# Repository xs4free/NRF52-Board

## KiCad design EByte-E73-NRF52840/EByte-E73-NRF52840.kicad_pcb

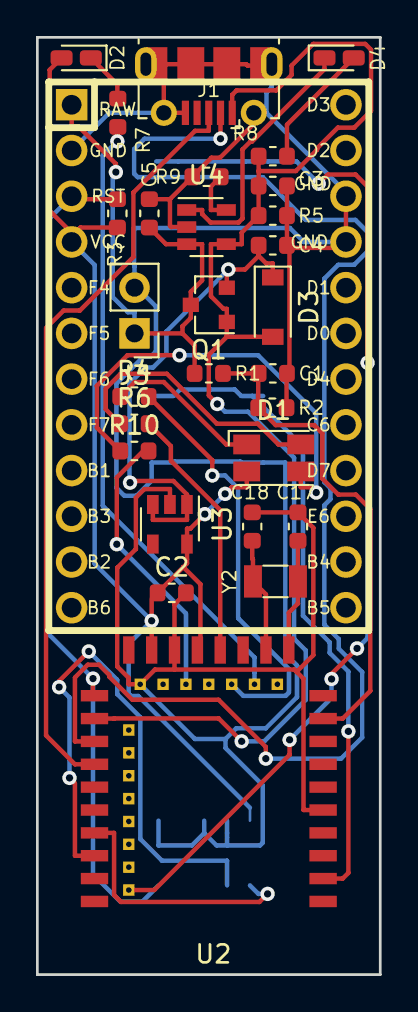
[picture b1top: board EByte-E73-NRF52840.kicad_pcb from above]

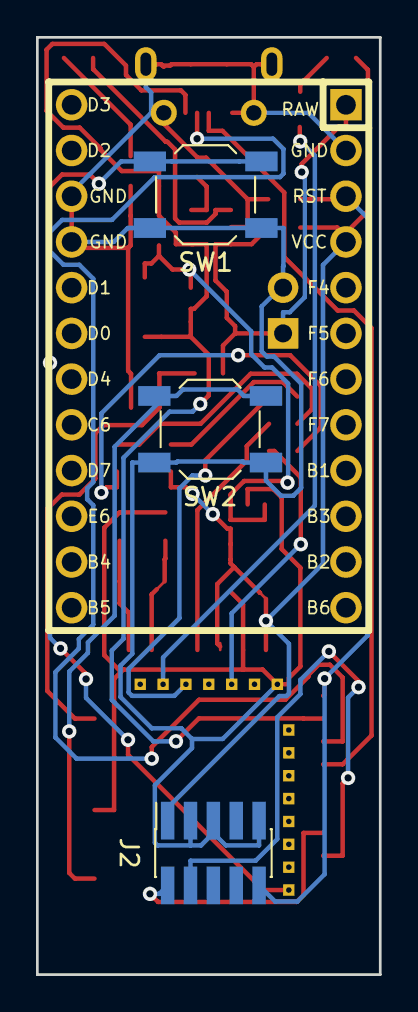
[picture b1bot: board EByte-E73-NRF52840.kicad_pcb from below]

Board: 2 copper layers, 19.1 x 52.1 mm, 32 parts (3 on the bottom side), 26 nets.

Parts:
C1: 1nF; C_0603_1608Metric
C2, C3, C4, C5: 10uF; C_0603_1608Metric
C17, C18: 12pF; C_0603_1608Metric
D1: HQ17-2303BGRC; LED_Avago_PLCC4_3.2x2.8mm_CW
D2, D4: LED; LED_0603_1608Metric_Castellated
D3: D_Schottky; D_SOD-123
J1: USB_B_Micro; USB_Micro-B_Molex-105017-0001
J2: SWD Header; PinSocket_2x05_P1.27mm_Vertical_SMD
J3: Conn_01x02; PinHeader_1x02_P2.54mm_Vertical
Q1: TP0610T; SOT-23
R1: 806k; R_0603_1608Metric
R2: 2M; R_0603_1608Metric
R3, R9: 10k; R_0603_1608Metric
R4: 1k2; R_0603_1608Metric
R5: 100k; R_0603_1608Metric
R6: 2k2; R_0603_1608Metric
R7, R8: 330; R_0603_1608Metric
R10: 330R; R_0603_1608Metric
SW1: DFU; SW_TACT_ALPS_SKQGABE010
SW2: FRST; SW_TACT_ALPS_SKQGABE010
U1: ProMicro; Pro_Micro
U2: E73-2G4M08S1C; 2G4M08S1C
U3: AP2112K-3.3; SOT-23-5
U4: TP4054ST; SOT-23-5
Y2: 32.768kHz; Crystal_SMD_3215-2Pin_3.2x1.5mm

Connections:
/D+: J1.3, U2.31
/D-: J1.2, U2.29
/LED1: R7.2, U2.14
/LED2B: R10.2, U2.20
/LED2G: R6.2, U2.17
/LED2R: R4.2, U2.16
/P0.31: C1.1, R1.2, R2.1, U2.9
/P1.10: SW2.2, U2.2
/RESET: J2.10, R3.2, U1.3, U2.26
/SW1: SW1.2, U2.42
/SWDCLK: J2.4, U2.39
/SWDIO: J2.2, U2.37
/VBatt: C5.1, J3.1, Q1.3, R1.1, U1.1, U4.3
/VBus: C3.1, D3.2, J1.1, Q1.1, R5.1, R8.2, U2.27, U4.4
GND: C1.2, C2.2, C3.2, C4.2, C5.2, C17.2, C18.2, J1.5, J1.6, J2.3, J2.5, J2.9, J3.2, R2.2, R5.2, R9.2, SW1.1, SW2.1, U1.2, U1.15, U1.16, U2.5, U2.21, U2.24, U3.2, U4.2
unnamed: C4.1, D3.1, Q1.2, U3.1, U3.3
unnamed: C17.1, U2.11, Y2.1
unnamed: C18.1, U2.13, Y2.2
unnamed: D1.1, R4.1
unnamed: D1.2, R6.1
unnamed: D1.3, R10.1
unnamed: D2.1, R7.1
unnamed: D4.1, U4.1
unnamed: D4.2, R8.1
unnamed: R9.1, U4.5
VDD: C2.1, D1.4, D2.2, J2.1, R3.1, U1.4, U2.19, U2.23, U3.5

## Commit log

2019-07-11 Moved components into PCB area and applied auto router for traces
